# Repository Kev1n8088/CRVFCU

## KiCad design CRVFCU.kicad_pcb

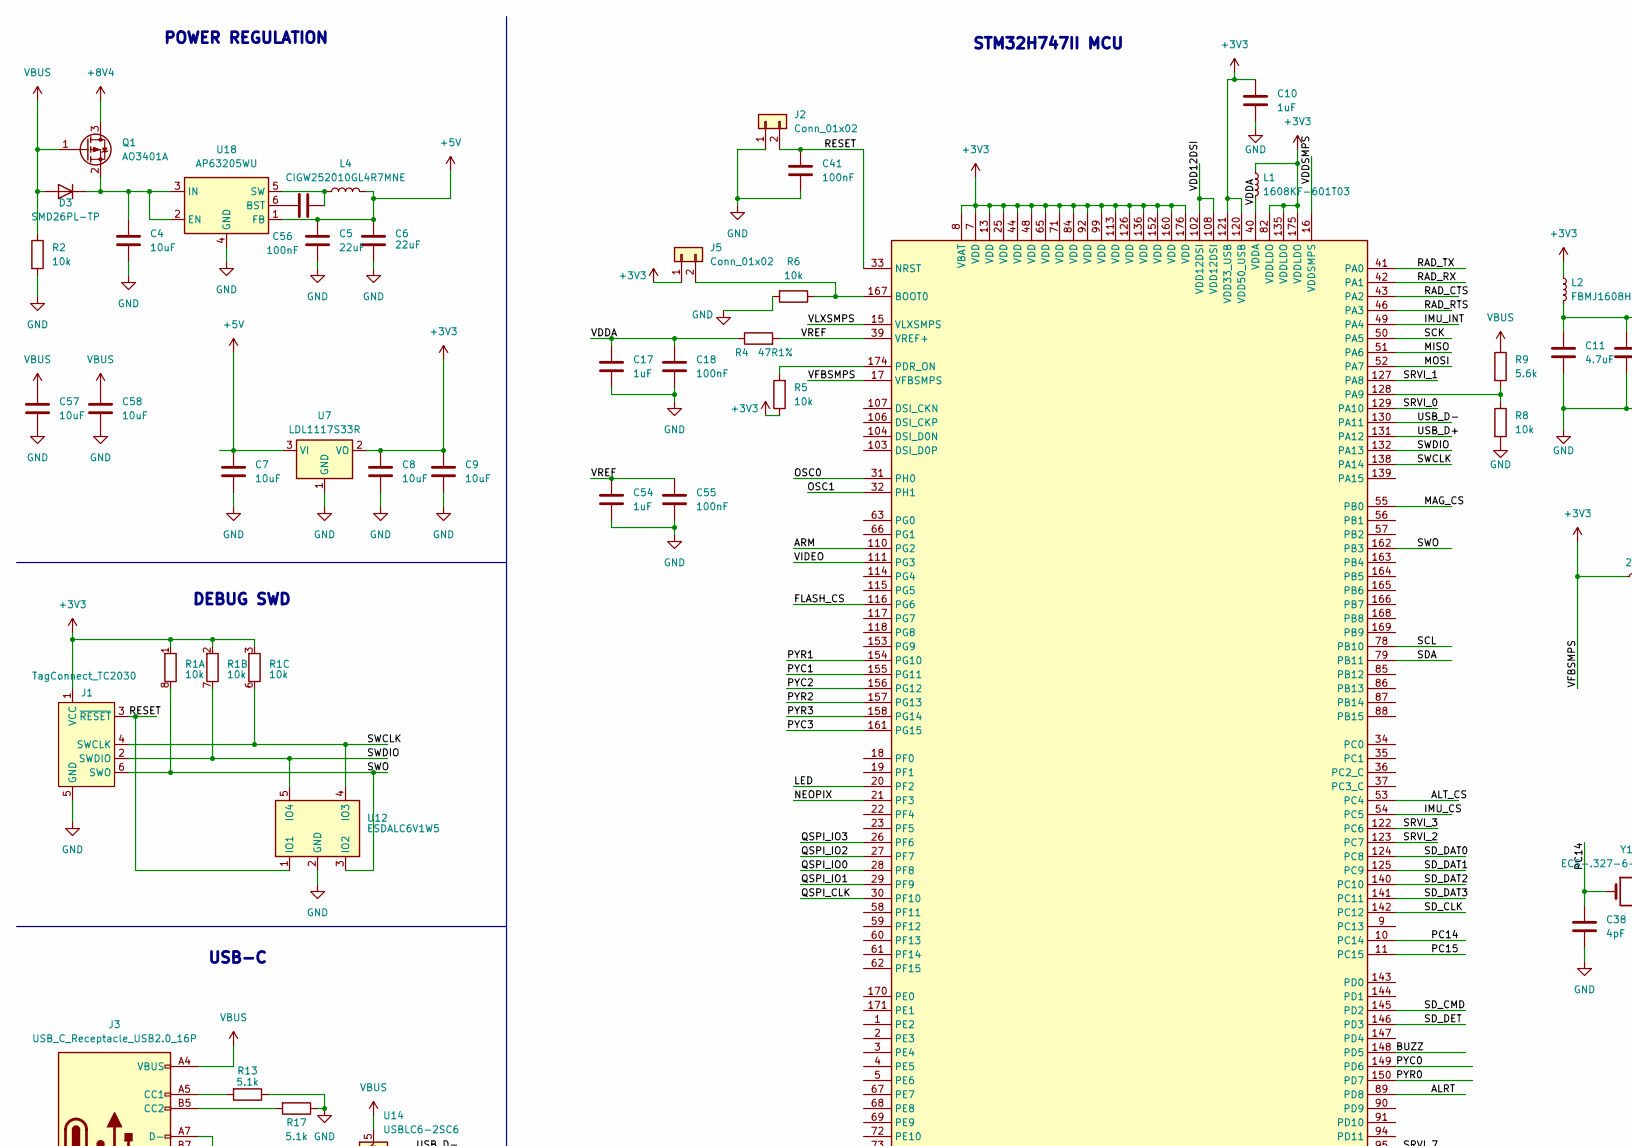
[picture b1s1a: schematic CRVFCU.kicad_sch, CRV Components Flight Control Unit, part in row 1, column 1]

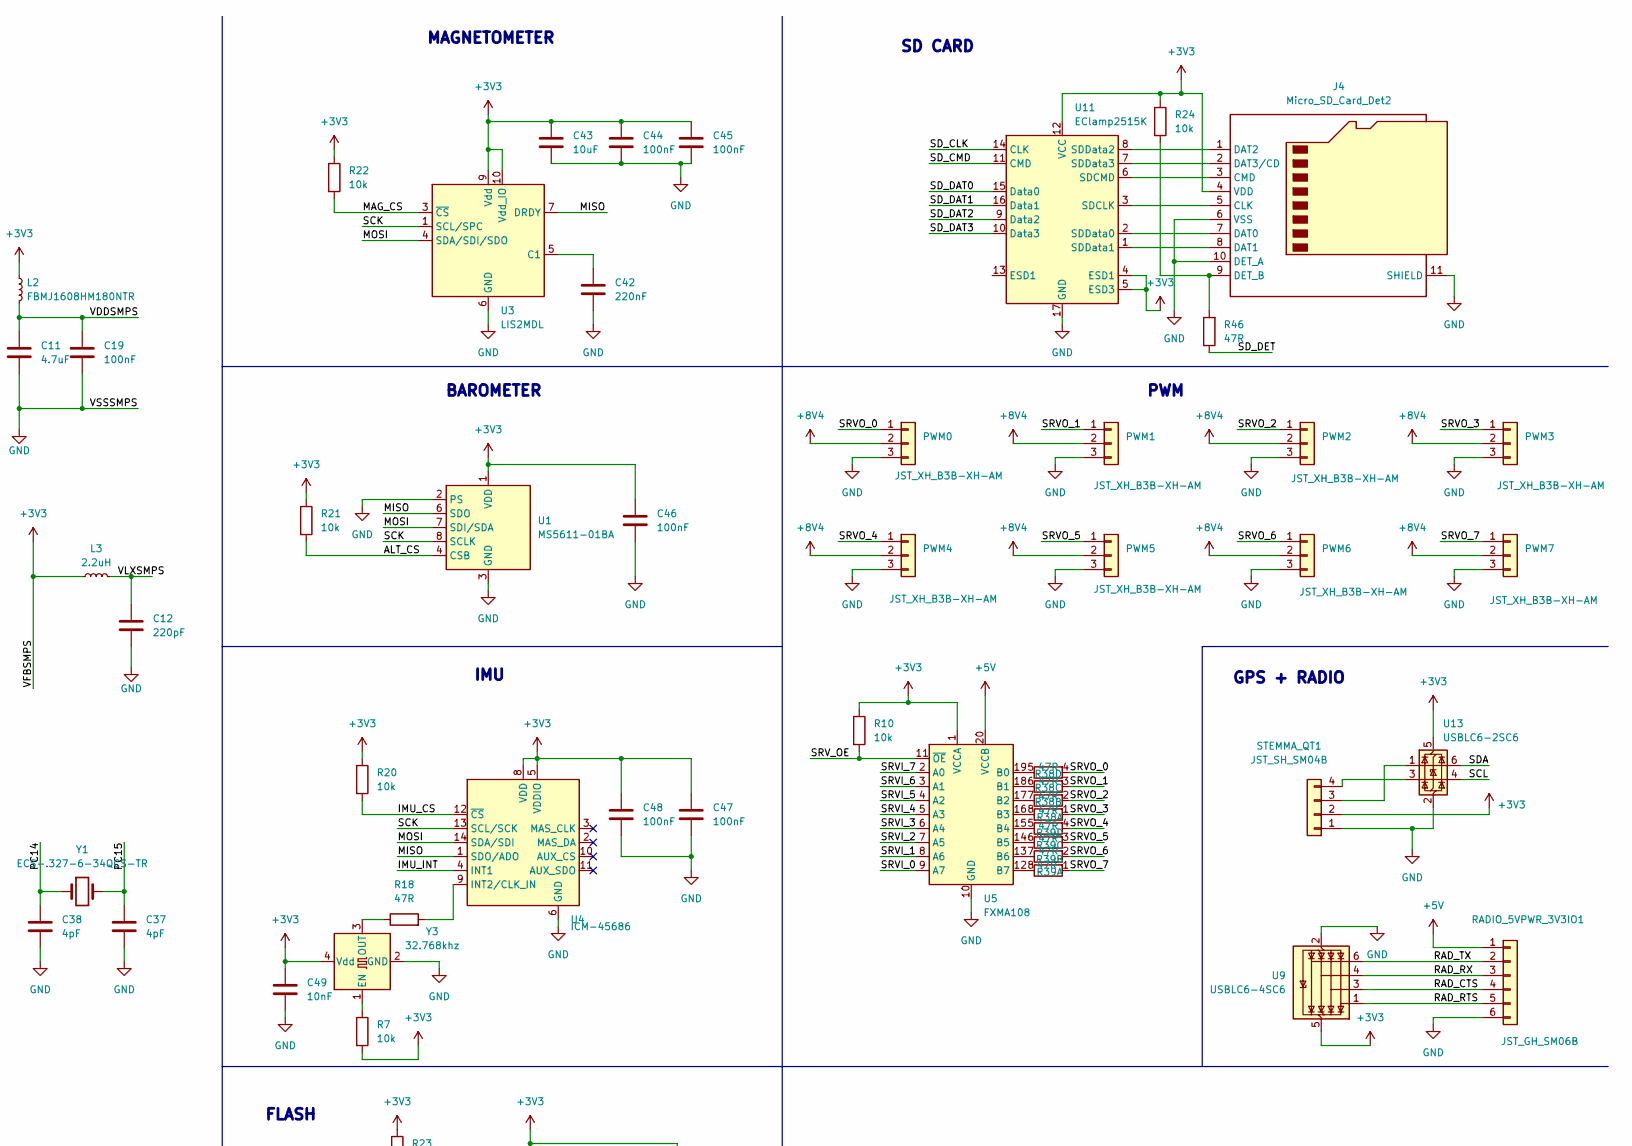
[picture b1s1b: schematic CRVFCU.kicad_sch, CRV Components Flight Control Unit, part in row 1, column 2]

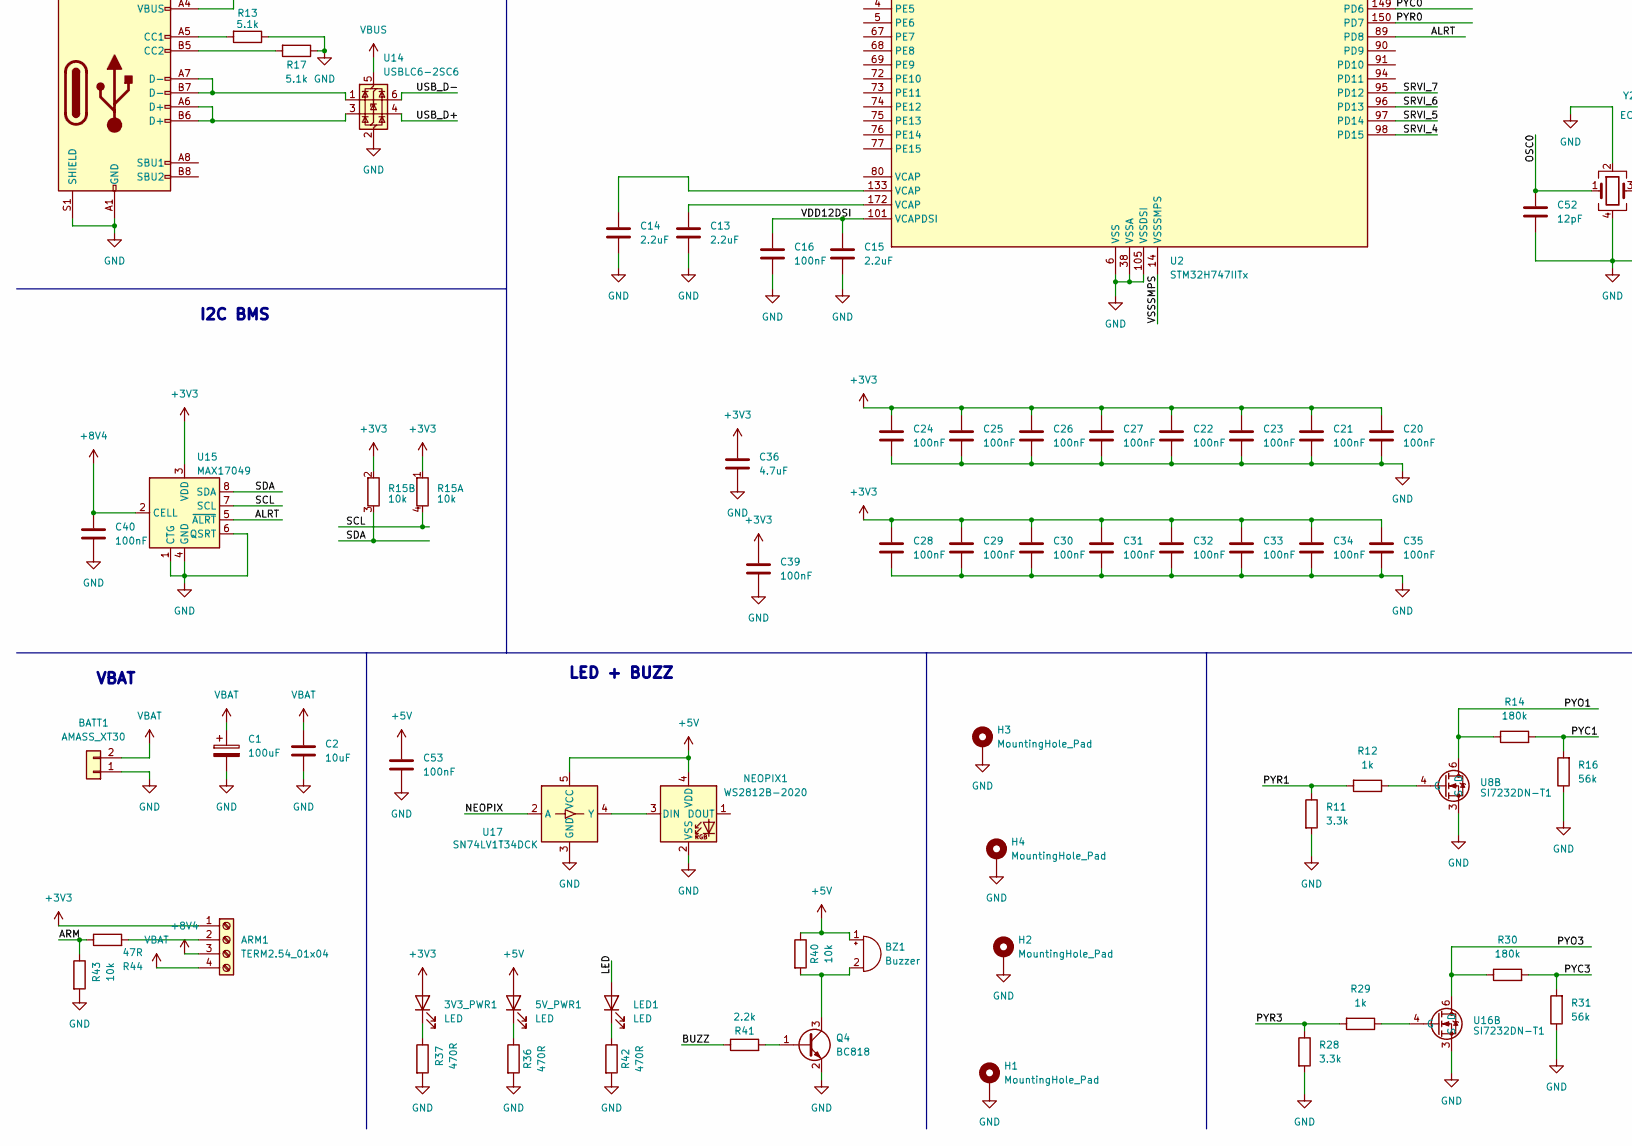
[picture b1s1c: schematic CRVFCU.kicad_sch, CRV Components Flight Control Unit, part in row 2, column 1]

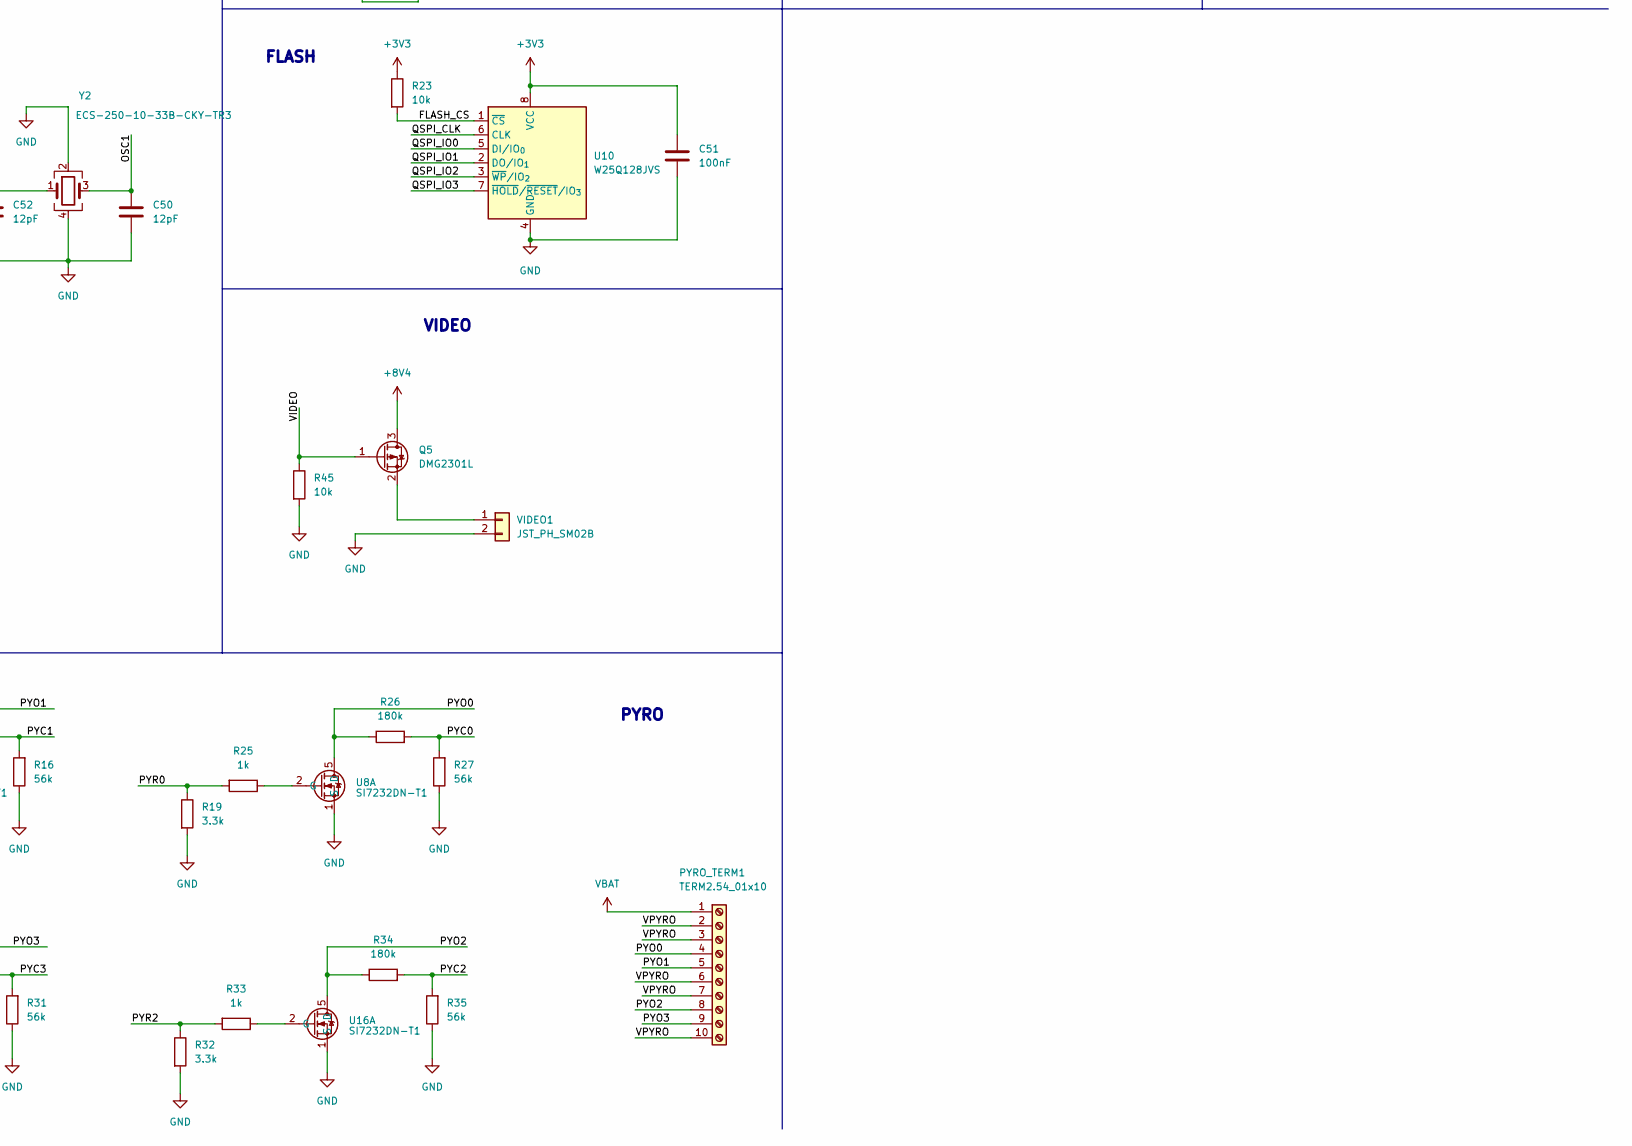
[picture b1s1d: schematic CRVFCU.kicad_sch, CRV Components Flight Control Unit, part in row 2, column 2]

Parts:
3V3_PWR1, 5V_PWR1: LED; LED_0603_1608Metric
ARM1: TERM2.54_01x04; TerminalBlock_TE_282834-4_1x04_P2.54mm_Horizontal
BATT1: AMASS_XT30; AMASS_XT30U-F_1x02_P5.0mm_Vertical
BZ1: Buzzer; Buzzer_CUI_CPT-9019S-SMT
C1: 100uF; CP_Radial_D8.0mm_P5.00mm
C2, C4, C7, C8, C9, C43, C57, C58: 10uF; C_0402_1005Metric
C5, C6: 22uF; C_0402_1005Metric
C10, C17, C54: 1uF; C_0402_1005Metric
C11, C36: 4.7uF; C_0402_1005Metric
C12: 220pF; C_0402_1005Metric
C13, C14, C15: 2.2uF; C_0402_1005Metric
C16, C18, C19, C20, C21, C22, C23, C24, C25, C26, C27, C28, C29, C30, C31, C32, C33, C34, C35, C39, C40, C41, C44, C45, C46, C47, C48, C51, C53, C55, C56: 100nF; C_0402_1005Metric
C37, C38: 4pF; C_0402_1005Metric
C42: 220nF; C_0402_1005Metric
C49: 10nF; C_0402_1005Metric
C50, C52: 12pF; C_0402_1005Metric
D3: SMD26PL-TP; D_SOD-123F
H1, H2, H3, H4: MountingHole_Pad; MountingHole_3.2mm_M3_Pad
J1: TagConnect_TC2030; Tag-Connect_TC2030-IDC-NL_2x03_P1.27mm_Vertical
J2, J5: Conn_01x02; PinHeader_1x02_P2.54mm_Vertical
J3: USB_C_Receptacle_USB2.0_16P; USB_C_Receptacle_GCT_USB4105-xx-A_16P_TopMnt_Horizontal
J4: Micro_SD_Card_Det2; microSD_HC_Hirose_DM3AT-SF-PEJM5
L1: 1608KF-601T03; L_0603_1608Metric
L2: FBMJ1608HM180NTR; L_0603_1608Metric
L3: 2.2uH; L_0603_1608Metric
L4: CIGW252010GL4R7MNE; L_1008_2520Metric
LED1: LED; LED_0603_1608Metric
NEOPIX1: WS2812B-2020; LED_WS2812B-2020_PLCC4_2.0x2.0mm
PWM0, PWM1, PWM2, PWM3, PWM4, PWM5, PWM6, PWM7: JST_XH_B3B-XH-AM; PinHeader_1x03_P2.54mm_Vertical
PYRO_TERM1: TERM2.54_01x10; TerminalBlock_TE_1-282834-0_1x10_P2.54mm_Horizontal
Q1: AO3401A; SOT-23
Q4: BC818; SOT-23
Q5: DMG2301L; SOT-23
R1: 10k; R_Array_Convex_4x0402
R2, R5, R6, R7, R8, R10, R20, R21, R22, R23, R24, R40, R43, R45: 10k; R_0402_1005Metric
R4: 47R1%; R_0402_1005Metric
R9: 5.6k; R_0402_1005Metric
R11, R19, R28, R32: 3.3k; R_0402_1005Metric
R12, R25, R29, R33: 1k; R_0402_1005Metric
R13, R17: 5.1k; R_0402_1005Metric
R14, R26, R30, R34: 180k; R_0402_1005Metric
R15: 10k; R_Array_Convex_2x0402
R16, R27, R31, R35: 56k; R_0402_1005Metric
R18, R44, R46: 47R; R_0402_1005Metric
R36, R37, R42: 470R; R_0402_1005Metric
R38, R39: 47R; R_Array_Convex_4x0402
R41: 2.2k; R_0402_1005Metric
RADIO_5VPWR_3V3IO1: JST_GH_SM06B; JST_GH_SM06B-GHS-TB_1x06-1MP_P1.25mm_Horizontal
STEMMA_QT1: JST_SH_SM04B; JST_SH_SM04B-SRSS-TB_1x04-1MP_P1.00mm_Horizontal
U1: MS5611-01BA; LGA-8_3x5mm_P1.25mm
U2: STM32H747IITx; LQFP-176_24x24mm_P0.5mm
U3: LIS2MDL; LGA-12_2x2mm_P0.5mm
U4: ICM-45686; LGA-14_3x2.5mm_P0.5mm_LayoutBorder3x4y
U5: FXMA108; WQFN-20-1EP_2.5x4.5mm_P0.5mm_EP1x2.9mm
U7: LDL1117S33R; SOT-223-3_TabPin2
U8, U16: SI7232DN-T1; PowerPak1212-8-Dual
U9: USBLC6-4SC6; SOT-23-6
U10: W25Q128JVS; SOIC-8_5.3x5.3mm_P1.27mm
U11: EClamp2515K; OnSemi_UDFN-16-1EP_1.35x3.3mm_P0.4mm_EP0.4x2.8mm
U12: ESDALC6V1W5; SOT-353_SC-70-5
U13, U14: USBLC6-2SC6; SOT-23-6
U15: MAX17049; TDFN-8-1EP_2x2mm_P0.5mm_EP0.8x1.2mm
U17: SN74LV1T34DCK; SOT-353_SC-70-5
U18: AP63205WU; TSOT-23-6
VIDEO1: JST_PH_SM02B; JST_PH_B2B-PH-K_1x02_P2.00mm_Vertical
Y1: ECS-.327-6-34QCS-TR; Crystal_SMD_3215-2Pin_3.2x1.5mm
Y2: ECS-250-10-33B-CKY-TR3; Crystal_SMD_3225-4Pin_3.2x2.5mm
Y3: 32.768khz; Oscillator_SMD_Abracon_ASE-4Pin_3.2x2.5mm

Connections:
+3V3: 3V3_PWR1.2 (A), ARM1.1, C8.1, C9.1, C10.1, C20.1, C21.1, C22.1, C23.1, C24.1, C25.1, C26.1, C27.1, C28.1, C29.1, C30.1, C31.1, C32.1, C33.1, C34.1, C35.1, C36.1, C39.1, C43.1, C44.1, C45.1, C46.1, C47.1, C48.1, C49.1, C51.1, J1.1 (VCC), J4.4 (VDD), J5.1, L1.1, L2.1, L3.1, R1.1, R1.2, R1.3, R5.1, R7.2, R10.1, R15.1, R15.2, R20.1, R21.1, R22.1, R23.1, R24.1, STEMMA_QT1.2, U1.1 (VDD), U2.7 (VDD), U2.8 (VBAT), U2.13 (VDD), U2.17 (VFBSMPS), U2.25 (VDD), U2.44 (VDD), U2.48 (VDD), U2.65 (VDD), U2.71 (VDD), U2.82 (VDDLDO), U2.84 (VDD), U2.92 (VDD), U2.99 (VDD), U2.113 (VDD), U2.120 (VDD50_USB), U2.121 (VDD33_USB), U2.126 (VDD), U2.135 (VDDLDO), U2.136 (VDD), U2.152 (VDD), U2.160 (VDD), U2.175 (VDDLDO), U2.176 (VDD), U3.9 (Vdd), U3.10 (Vdd_IO), U4.5 (VDDIO), U4.8 (VDD), U5.1 (VCCA), U7.2 (VO), U9.5 (VBUS), U10.8 (VCC), U11.4 (ESD1), U11.5 (ESD3), U11.12 (VCC), U13.5 (VBUS), U15.3 (VDD), Y3.4 (Vdd)
+5V: 5V_PWR1.2 (A), BZ1.1 (+), C5.1, C6.1, C7.1, C53.1, L4.2, NEOPIX1.4 (VDD), R40.1, RADIO_5VPWR_3V3IO1.1, U5.20 (VCCB), U7.3 (VI), U17.5 (VCC), U18.1 (FB)
+8V4: ARM1.3, C40.1, PWM0.2, PWM1.2, PWM2.2, PWM3.2, PWM4.2, PWM5.2, PWM6.2, PWM7.2, Q1.3 (D), Q5.3 (D), U15.2 (CELL)
/ALRT: U2.89 (PD8), U15.5 (~ALRT)
/ALT_CS: R21.2, U1.4 (CSB), U1.5 (CSB), U2.53 (PC4)
/ARM: R43.1, R44.1, U2.110 (PG2)
/BUZZ: R41.1, U2.148 (PD5)
/FLASH_CS: R23.2, U2.116 (PG6), U10.1 (~CS)
/IMU_CS: R20.2, U2.54 (PC5), U4.12 (~CS)
/IMU_INT: U2.49 (PA4), U4.4 (INT1)
/LED: LED1.2 (A), U2.20 (PF2)
/MAG_CS: R22.2, U2.55 (PB0), U3.3 (~CS)
/MISO: U1.6 (SDO), U2.51 (PA6), U3.7 (DRDY), U4.1 (SDO/ADO)
/MOSI: U1.7 (SDI/SDA), U2.52 (PA7), U3.4 (SDA/SDI/SDO), U4.14 (SDA/SDI)
/NEOPIX: U2.21 (PF3), U17.2 (A)
/OSC0: C52.1, U2.31 (PH0), Y2.1
/OSC1: C50.1, U2.32 (PH1), Y2.3
/PC14: C38.1, U2.10 (PC14), Y1.1
/PC15: C37.1, U2.11 (PC15), Y1.2
/PYC0: R26.2, R27.2, U2.149 (PD6)
/PYC1: R14.2, R16.2, U2.155 (PG11)
/PYC2: R34.2, R35.2, U2.156 (PG12)
/PYC3: R30.2, R31.2, U2.161 (PG15)
/PYO0: PYRO_TERM1.4, R26.1, U8.5 (D)
/PYO1: PYRO_TERM1.5, R14.1, U8.6 (D)
/PYO2: PYRO_TERM1.8, R34.1, U16.5 (D)
/PYO3: PYRO_TERM1.9, R30.1, U16.6 (D)
/PYR0: R19.1, R25.2, U2.150 (PD7)
/PYR1: R11.1, R12.2, U2.154 (PG10)
/PYR2: R32.1, R33.2, U2.157 (PG13)
/PYR3: R28.1, R29.2, U2.158 (PG14)
/QSPI_CLK: U2.30 (PF10), U10.6 (CLK)
/QSPI_IO0: U2.28 (PF8), U10.5 (DI/IO_{0})
/QSPI_IO1: U2.29 (PF9), U10.2 (DO/IO_{1})
/QSPI_IO2: U2.27 (PF7), U10.3 (~WP/IO_{2})
/QSPI_IO3: U2.26 (PF6), U10.7 (~HOLD/~RESET/IO_{3})
/RAD_CTS: RADIO_5VPWR_3V3IO1.4, U2.43 (PA2), U9.3 (I/O2)
/RAD_RTS: RADIO_5VPWR_3V3IO1.5, U2.46 (PA3), U9.1 (I/O1)
/RAD_RX: RADIO_5VPWR_3V3IO1.3, U2.42 (PA1), U9.4 (I/O3)
/RAD_TX: RADIO_5VPWR_3V3IO1.2, U2.41 (PA0), U9.6 (I/O4)
/RESET: C41.2, J1.3 (~RESET), J2.2, U2.33 (NRST), U12.1 (IO1)
/SCK: U1.8 (SCLK), U2.50 (PA5), U3.1 (SCL/SPC), U4.13 (SCL/SCK)
/SCL: R15.4, U2.78 (PB10), U13.4 (I/O2), U15.7 (SCL)
/SDA: R15.3, U2.79 (PB11), U13.6 (I/O1), U15.8 (SDA)
/SD_CLK: U2.142 (PC12), U11.14 (CLK)
/SD_CMD: U2.145 (PD2), U11.11 (CMD)
/SD_DAT0: U2.124 (PC8), U11.15 (Data0)
/SD_DAT1: U2.125 (PC9), U11.16 (Data1)
/SD_DAT2: U2.140 (PC10), U11.9 (Data2)
/SD_DAT3: U2.141 (PC11), U11.10 (Data3)
/SD_DET: R46.1, U2.146 (PD3)
/SRVI_0: U2.129 (PA10), U5.9 (A7)
/SRVI_1: U2.127 (PA8), U5.8 (A6)
/SRVI_2: U2.123 (PC7), U5.7 (A5)
/SRVI_3: U2.122 (PC6), U5.6 (A4)
/SRVI_4: U2.98 (PD15), U5.5 (A3)
/SRVI_5: U2.97 (PD14), U5.4 (A2)
/SRVI_6: U2.96 (PD13), U5.3 (A1)
/SRVI_7: U2.95 (PD12), U5.2 (A0)
/SRVO_0: PWM0.1, R38.4
/SRVO_1: PWM1.1, R38.3
/SRVO_2: PWM2.1, R38.2
/SRVO_3: PWM3.1, R38.1
/SRVO_4: PWM4.1, R39.4
/SRVO_5: PWM5.1, R39.3
/SRVO_6: PWM6.1, R39.2
/SRVO_7: PWM7.1, R39.1
/SRV_OE: R10.2, U5.11 (~OE)
/SWCLK: J1.4 (SWCLK), R1.6, U2.138 (PA14), U12.4 (IO3)
/SWDIO: J1.2 (SWDIO), R1.7, U2.132 (PA13), U12.5 (IO4)
/SWO: J1.6 (SWO), R1.8, U2.162 (PB3), U12.3 (IO2)
/USB_D+: U2.131 (PA12), U14.4 (I/O2)
/USB_D-: U2.130 (PA11), U14.6 (I/O1)
/VDD12DSI: C15.1, C16.1, U2.101 (VCAPDSI), U2.102 (VDD12DSI), U2.108 (VDD12DSI)
/VDDA: C17.1, C18.1, L1.2, R4.1, U2.40 (VDDA)
/VDDSMPS: C11.1, C19.1, L2.2, U2.16 (VDDSMPS)
/VIDEO: Q5.1 (G), R45.1, U2.111 (PG3)
/VLXSMPS: C12.2, L3.2, U2.15 (VLXSMPS)
/VPYRO: PYRO_TERM1.2, PYRO_TERM1.3, PYRO_TERM1.6, PYRO_TERM1.7, PYRO_TERM1.10
/VREF: C54.1, C55.1, R4.2, U2.39 (VREF+)
GND: BATT1.1, C1.2, C2.2, C4.2, C5.2, C6.2, C7.2, C8.2, C9.2, C10.2, C11.2, C12.1, C13.2, C14.2, C15.2, C16.2, C17.2, C18.2, C19.2, C20.2, C21.2, C22.2, C23.2, C24.2, C25.2, C26.2, C27.2, C28.2, C29.2, C30.2, C31.2, C32.2, C33.2, C34.2, C35.2, C36.2, C37.2, C38.2, C39.2, C40.2, C41.1, C42.2, C43.2, C44.2, C45.2, C46.2, C47.2, C48.2, C49.2, C50.2, C51.2, C52.2, C53.2, C54.2, C55.2, C57.2, C58.2, H1.1, H2.1, H3.1, H4.1, J1.5 (GND), J2.1, J3.A1 (GND), J3.A12 (GND), J3.B1 (GND), J3.B12 (GND), J3.S1 (SHIELD), J4.6 (VSS), J4.10 (DET_A), J4.11 (SHIELD), NEOPIX1.2 (VSS), PWM0.3, PWM1.3, PWM2.3, PWM3.3, PWM4.3, PWM5.3, PWM6.3, PWM7.3, Q4.2 (E), R2.2, R6.2, R8.2, R11.2, R13.1, R16.1, R17.1, R19.2, R27.1, R28.2, R31.1, R32.2, R35.1, R36.2, R37.2, R42.2, R43.2, R45.2, RADIO_5VPWR_3V3IO1.6, STEMMA_QT1.1, U1.2 (PS), U1.3 (GND), U2.6 (VSS), U2.12 (VSS), U2.14 (VSSSMPS), U2.24 (VSS), U2.38 (VSSA), U2.45 (VSS), U2.47 (VSS), U2.64 (VSS), U2.70 (VSS), U2.81 (VSS), U2.83 (VSS), U2.93 (VSS), U2.100 (VSS), U2.105 (VSSDSI), U2.109 (VSSDSI), U2.112 (VSS), U2.119 (VSS), U2.134 (VSS), U2.137 (VSS), U2.151 (VSS), U2.159 (VSS), U2.173 (VSS), U3.6 (GND), U3.8 (GND), U4.6 (GND), U5.10 (GND), U7.1 (GND), U8.1 (S), U8.3 (S), U9.2 (GND), U10.4 (GND), U11.17 (GND), U12.2 (GND), U13.2 (GND), U14.2 (GND), U15.1 (CTG), U15.4 (GND), U15.6 (QSRT), U16.1 (S), U16.3 (S), U17.3 (GND), U18.4 (GND), VIDEO1.2, Y2.2, Y2.4, Y3.2 (GND)
unnamed: 3V3_PWR1.1 (K), R37.1
unnamed: 5V_PWR1.1 (K), R36.1
unnamed: ARM1.2, R44.2
unnamed: BZ1.2 (-), Q4.3 (C), R40.2
unnamed: C13.1, U2.172 (VCAP)
unnamed: C14.1, U2.133 (VCAP)
unnamed: C4.1, D3.1 (K), Q1.2 (S), U18.2 (EN), U18.3 (IN)
unnamed: J3.A5 (CC1), R13.2
unnamed: J3.B5 (CC2), R17.2
unnamed: J3.A6 (D+), J3.B6 (D+), U14.3 (I/O2)
unnamed: J3.A7 (D-), J3.B7 (D-), U14.1 (I/O1)
unnamed: J4.5 (CLK), U11.3 (SDCLK)
unnamed: J4.3 (CMD), U11.6 (SDCMD)
unnamed: J4.7 (DAT0), U11.2 (SDData0)
unnamed: J4.8 (DAT1), U11.1 (SDData1)
unnamed: J4.1 (DAT2), U11.8 (SDData2)
unnamed: J4.2 (DAT3/CD), U11.7 (SDData3)
unnamed: J4.9 (DET_B), R24.2, R46.2
unnamed: J5.2, R6.1, U2.167 (BOOT0)
unnamed: LED1.1 (K), R42.1
unnamed: NEOPIX1.3 (DIN), U17.4 (Y)
unnamed: Q4.1 (B), R41.2
unnamed: Q5.2 (S), VIDEO1.1
unnamed: STEMMA_QT1.3, U13.1 (I/O1)
unnamed: STEMMA_QT1.4, U13.3 (I/O2)
unnamed: R8.1, R9.2, U2.128 (PA9)
unnamed: R5.2, U2.174 (PDR_ON)
unnamed: C42.1, U3.5 (C1)
unnamed: R18.2, U4.9 (INT2/CLK_IN)
unnamed: R38.5, U5.19 (B0)
unnamed: R38.6, U5.18 (B1)
unnamed: R38.7, U5.17 (B2)
unnamed: R38.8, U5.16 (B3)
unnamed: R39.5, U5.15 (B4)
unnamed: R39.6, U5.14 (B5)
unnamed: R39.7, U5.13 (B6)
unnamed: R39.8, U5.12 (B7)
unnamed: R25.1, U8.2 (G)
unnamed: R12.1, U8.4 (G)
unnamed: R33.1, U16.2 (G)
unnamed: R29.1, U16.4 (G)
unnamed: C56.1, U18.6 (BST)
unnamed: C56.2, L4.1, U18.5 (SW)
unnamed: R7.1, Y3.1 (EN)
unnamed: R18.1, Y3.3 (OUT)
VBAT: ARM1.4, BATT1.2, C1.1, C2.1, PYRO_TERM1.1
VBUS: C57.1, C58.1, D3.2 (A), J3.A4 (VBUS), J3.A9 (VBUS), J3.B4 (VBUS), J3.B9 (VBUS), Q1.1 (G), R2.1, R9.1, U14.5 (VBUS)

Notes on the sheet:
STM32H747II MCU
PYRO
IMU
PWM
GPS + RADIO
VIDEO
I2C BMS
DEBUG SWD
MAGNETOMETER
BAROMETER
SD CARD
FLASH
VBAT
USB-C
LED + BUZZ
POWER REGULATION

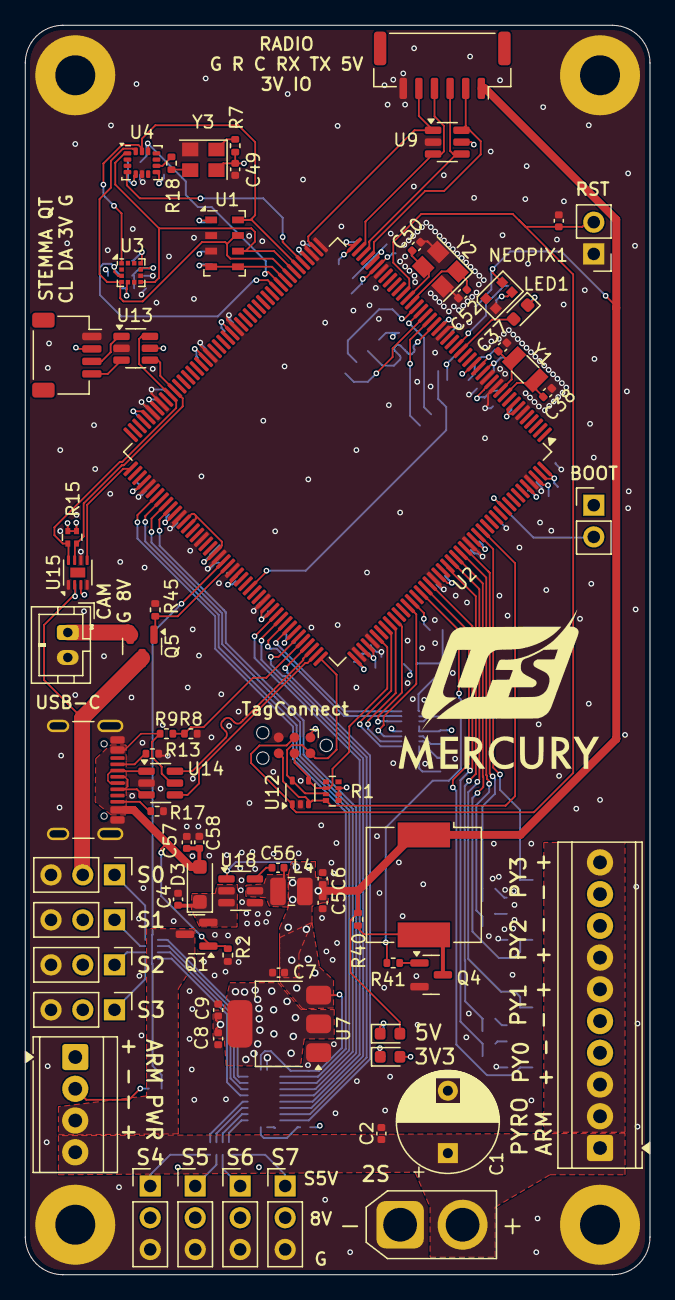
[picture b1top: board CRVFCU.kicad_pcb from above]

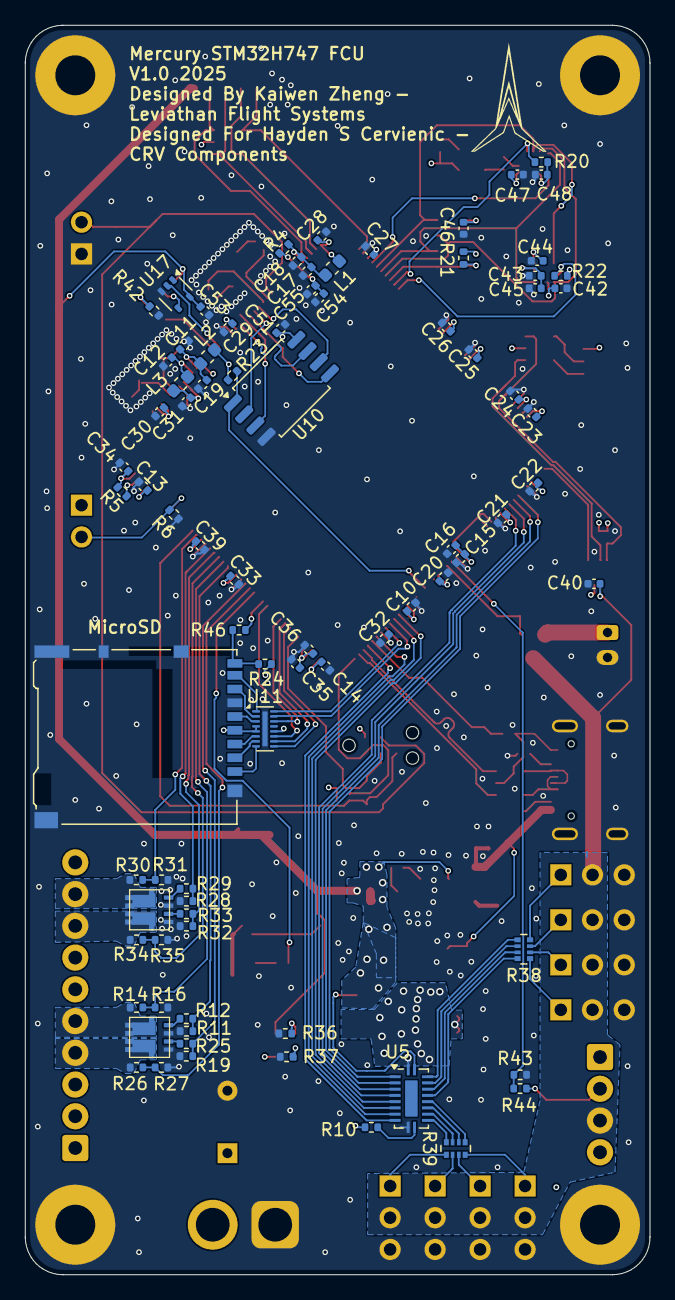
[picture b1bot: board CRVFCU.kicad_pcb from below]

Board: 4 copper layers, 50.0 x 100.0 mm, 158 parts (83 on the bottom side), 128 nets.

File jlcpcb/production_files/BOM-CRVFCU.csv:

Comment,Designator,Footprint,LCSC,Quantity
SI7232DN-T1,U16,PowerPak1212-8-Dual,,1
SI7232DN-T1,U8,PowerPak1212-8-Dual,,1
Buzzer,BZ1,Buzzer_CUI_CPT-9019S-SMT,,1
LED,5V_PWR1,LED_0603_1608Metric,,1
220R,R36,R_0402_1005Metric,,1
LED,3V3_PWR1,LED_0603_1608Metric,,1
100uF,C1,CP_Radial_D8.0mm_P5.00mm,,1
AMASS_XT30,BATT1,AMASS_XT30U-F_1x02_P5.0mm_Vertical,,1
10uF,C2,C_0402_1005Metric,,1
220R,R37,R_0402_1005Metric,,1
TERM2.54_01x10,PYRO_TERM1,TerminalBlock_TE_1-282834-0_1x10_P2.54mm_Horizontal,,1
DMG2301L,Q3,SOT-23,,1
100nF,C40,C_0402_1005Metric,,1
~,U12,SOT-353_SC-70-5,,1
10k,R1,R_Array_Convex_4x0402,,1
CM1624,U11,OnSemi_UDFN-16-1EP_1.35x3.3mm_P0.4mm_EP0.4x2.8mm,,1
Micro_SD_Card_Det2,J4,microSD_HC_Hirose_DM3AT-SF-PEJM5,,1
10k,R24,R_0402_1005Metric,,1
W25Q128JVS,U10,SOIC-8_5.3x5.3mm_P1.27mm,,1
32.768khz,Y1,Crystal_SMD_3215-2Pin_3.2x1.5mm,,1
USBLC6-2SC6,U14,SOT-23-6,,1
ASE-25.000MHZ,Y4,Oscillator_SMD_Abracon_ASE-4Pin_3.2x2.5mm,,1
10uF,C17,C_0402_1005Metric,,1
100nF,C16,C_0402_1005Metric,,1
100nF,C20,C_0402_1005Metric,,1
1uF,C10,C_0402_1005Metric,,1
220pF,C12,C_0402_1005Metric,,1
2.2uF,C13,C_0402_1005Metric,,1
2.2uF,C15,C_0402_1005Metric,,1
4.7uF,C11,C_0402_1005Metric,,1
2.2uF,C14,C_0402_1005Metric,,1
100nF,C19,C_0402_1005Metric,,1
100nF,C18,C_0402_1005Metric,,1
100nF,C22,C_0402_1005Metric,,1
100nF,C27,C_0402_1005Metric,,1
100nF,C24,C_0402_1005Metric,,1
100nF,C32,C_0402_1005Metric,,1
100nF,C21,C_0402_1005Metric,,1
100nF,C23,C_0402_1005Metric,,1
100nF,C25,C_0402_1005Metric,,1
100nF,C26,C_0402_1005Metric,,1
100nF,C29,C_0402_1005Metric,,1
100nF,C30,C_0402_1005Metric,,1
100nF,C31,C_0402_1005Metric,,1
100nF,C28,C_0402_1005Metric,,1
100nF,C41,C_0402_1005Metric,,1
4.7uF,C36,C_0402_1005Metric,,1
1.5pF,C37,C_0402_1005Metric,,1
100nF,C33,C_0402_1005Metric,,1
100nF,C34,C_0402_1005Metric,,1
100nF,C35,C_0402_1005Metric,,1
1.5pF,C38,C_0402_1005Metric,,1
100nF,C51,C_0402_1005Metric,,1
2.2uH,L3,L_0603_1608Metric,,1
100nF,C50,C_0402_1005Metric,,1
USB_C_Receptacle_USB2.0_16P,J3,USB_C_Receptacle_GCT_USB4105-xx-A_16P_TopMnt_Horizontal,,1
1608KF-601T03,L1,L_0603_1608Metric,,1
FBMJ1608HM180NTR,L2,L_0603_1608Metric,,1
10k,R9,R_0402_1005Metric,,1
47R1%,R4,R_0402_1005Metric,,1
10k,R5,R_0402_1005Metric,,1
10k,R6,R_0402_1005Metric,,1
51,R8,R_0402_1005Metric,,1
5.1k,R17,R_0402_1005Metric,,1
5.1k,R13,R_0402_1005Metric,,1
10k,R23,R_0402_1005Metric,,1
STM32H747IITx,U2,LQFP-176_24x24mm_P0.5mm,,1
100nF,C39,C_0402_1005Metric,,1
SW_Omron_B3FS,SW1,SW_SPST_FSMSM,,1
SW_Nidec_CAS-120A1,SW2,Nidec_Copal_CAS-120A,,1
AP1117-33,U7,SOT-223-3_TabPin2,,1
10uF,C4,C_0402_1005Metric,,1
10uF,C5,C_0402_1005Metric,,1
10uF,C9,C_0402_1005Metric,,1
10uF,C8,C_0402_1005Metric,,1
10uF,C6,C_0402_1005Metric,,1
10uF,C7,C_0402_1005Metric,,1
MBR0540,D1,D_SOD-123,,1
MBR0540,D2,D_SOD-123,,1
10k,R2,R_0402_1005Metric,,1
AP1117-50,U6,SOT-223-3_TabPin2,,1
SN74LV1T34DCK,U17,SOT-353_SC-70-5,,1
WS2812B-2020,NEOPIX1,LED_WS2812B-2020_PLCC4_2.0x2.0mm,,1
TERM2.54_01x04,ARM1,TerminalBlock_TE_282834-4_1x04_P2.54mm_Horizontal,,1
JST_XH_B3B-XH-AM,PWM0,PinHeader_1x03_P2.54mm_Vertical,,1
JST_XH_B3B-XH-AM,PWM3,PinHeader_1x03_P2.54mm_Vertical,,1
JST_XH_B3B-XH-AM,PWM2,PinHeader_1x03_P2.54mm_Vertical,,1
JST_XH_B3B-XH-AM,PWM1,PinHeader_1x03_P2.54mm_Vertical,,1
32.768khz,Y3,Oscillator_SMD_Abracon_ASE-4Pin_3.2x2.5mm,,1
JST_GH_SM02B,VIDEO1,JST_GH_SM02B-GHS-TB_1x02-1MP_P1.25mm_Horizontal,,1
MAX17049,U15,TDFN-8-1EP_2x2mm_P0.5mm_EP0.8x1.2mm,,1
USBLC6-4SC6,U9,SOT-23-6,,1
FXMA108,U5,WQFN-20-1EP_2.5x4.5mm_P0.5mm_EP1x2.9mm,,1
ICM-45686,U4,LGA-14_3x2.5mm_P0.5mm_LayoutBorder3x4y,,1
LIS2MDL,U3,LGA-12_2x2mm_P0.5mm,,1
MS5611-01BA,U1,LGA-8_3x5mm_P1.25mm,,1
JST_SH_SM04B,STEMMA_QT1,JST_SH_SM04B-SRSS-TB_1x04-1MP_P1.00mm_Horizontal,,1
JST_GH_SM06B,RADIO_5VPWR_3V3IO1,JST_GH_SM06B-GHS-TB_1x06-1MP_P1.25mm_Horizontal,,1
10k,R45,R_0402_1005Metric,,1
47R,R44,R_0402_1005Metric,,1
10k,R43,R_0402_1005Metric,,1
220R,R42,R_0402_1005Metric,,1
2.2k,R41,R_0402_1005Metric,,1
10k,R40,R_0402_1005Metric,,1
47R,R39,R_Array_Convex_4x0402,,1
47R,R38,R_Array_Convex_4x0402,,1
56k,R35,R_0402_1005Metric,,1
180k,R34,R_0402_1005Metric,,1
1k,R33,R_0402_1005Metric,,1
3.3k,R32,R_0402_1005Metric,,1
56k,R31,R_0402_1005Metric,,1
180k,R30,R_0402_1005Metric,,1
1k,R29,R_0402_1005Metric,,1
3.3k,R28,R_0402_1005Metric,,1
56k,R27,R_0402_1005Metric,,1
180k,R26,R_0402_1005Metric,,1
1k,R25,R_0402_1005Metric,,1
10k,R22,R_0402_1005Metric,,1
10k,R20,R_0402_1005Metric,,1
3.3k,R19,R_0402_1005Metric,,1
47R,R18,R_0402_1005Metric,,1
56k,R16,R_0402_1005Metric,,1
10k,R15,R_Array_Convex_2x0402,,1
180k,R14,R_0402_1005Metric,,1
1k,R12,R_0402_1005Metric,,1
3.3k,R11,R_0402_1005Metric,,1
10k,R10,R_0402_1005Metric,,1
10k,R7,R_0402_1005Metric,,1
DMG2301L,Q6,SOT-23,,1
DMG2301L,Q5,SOT-23,,1
BC818,Q4,SOT-23,,1
JST_XH_B3B-XH-AM,PWM7,PinHeader_1x03_P2.54mm_Vertical,,1
JST_XH_B3B-XH-AM,PWM6,PinHeader_1x03_P2.54mm_Vertical,,1
JST_XH_B3B-XH-AM,PWM5,PinHeader_1x03_P2.54mm_Vertical,,1
JST_XH_B3B-XH-AM,PWM4,PinHeader_1x03_P2.54mm_Vertical,,1
LED,LED1,LED_0603_1608Metric,,1
10nF,C49,C_0402_1005Metric,,1
100nF,C48,C_0402_1005Metric,,1
100nF,C47,C_0402_1005Metric,,1
100nF,C46,C_0402_1005Metric,,1
100nF,C45,C_0402_1005Metric,,1
100nF,C44,C_0402_1005Metric,,1
10uF,C43,C_0402_1005Metric,,1
220nF,C42,C_0402_1005Metric,,1
10k,R21,R_0402_1005Metric,,1
USBLC6-2SC6,U13,SOT-23-6,,1

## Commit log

2025-05-09 parts of initial schematic completed
2025-05-10 completed grouping in pcb, prep for route
2025-05-11 completed 50x100 routing, attempting 40mm
2025-05-11 added bom and changed 25mhz oscillator
2025-05-11 rounded corners, added silkscreens, fixed 25mhz oscillator, missing logos but basically finalized
2025-05-11 changed rst and boot to headers
2025-05-11 changed some small layout items and fixed drc
2025-05-11 made oscillator vias more standardized
2025-05-12 added vref caps and changed some cap values
2025-05-12 added backups
2025-05-12 adjusted crystals
2025-05-12 added silkscreens
2025-05-12 tuned silkscreens
2025-05-12 fixed drc silkscreens
2025-05-12 some more silkscreen changes
2025-05-12 changed silkscreens and via locations for aesthetics
2025-05-12 changed via sizes for manufacturing purposes and fixed drc
2025-05-12 changed hole clearance to 0.2mm and resolved drc
2025-05-12 changed edge clearance to 0.2mm
2025-05-13 changed constraints to allow for manufacturing by oshpark, drc resolved
2025-05-13 added gitignore
2025-05-13 changed color and adjusted some traces
2025-05-13 adjusted some vias
2025-05-13 added IMU directional indicator
2025-05-13 added some vias
2025-05-13 changed silkscreen slightly
2025-05-26 ensured all servo pins are PWM capable, and changed 5v LDO to buck
2025-05-26 added protection diode for buck and changed routing for thermal considerations
2025-05-26 changed to higher current mosfet for power supply switching and fixed silkscreens
2025-05-27 simplified power delivery
2025-05-28 adjusted usbc port and 5v pour dimensions
2025-06-09 added XYZ orientation sign
2025-06-09 changed cam to jst ph
